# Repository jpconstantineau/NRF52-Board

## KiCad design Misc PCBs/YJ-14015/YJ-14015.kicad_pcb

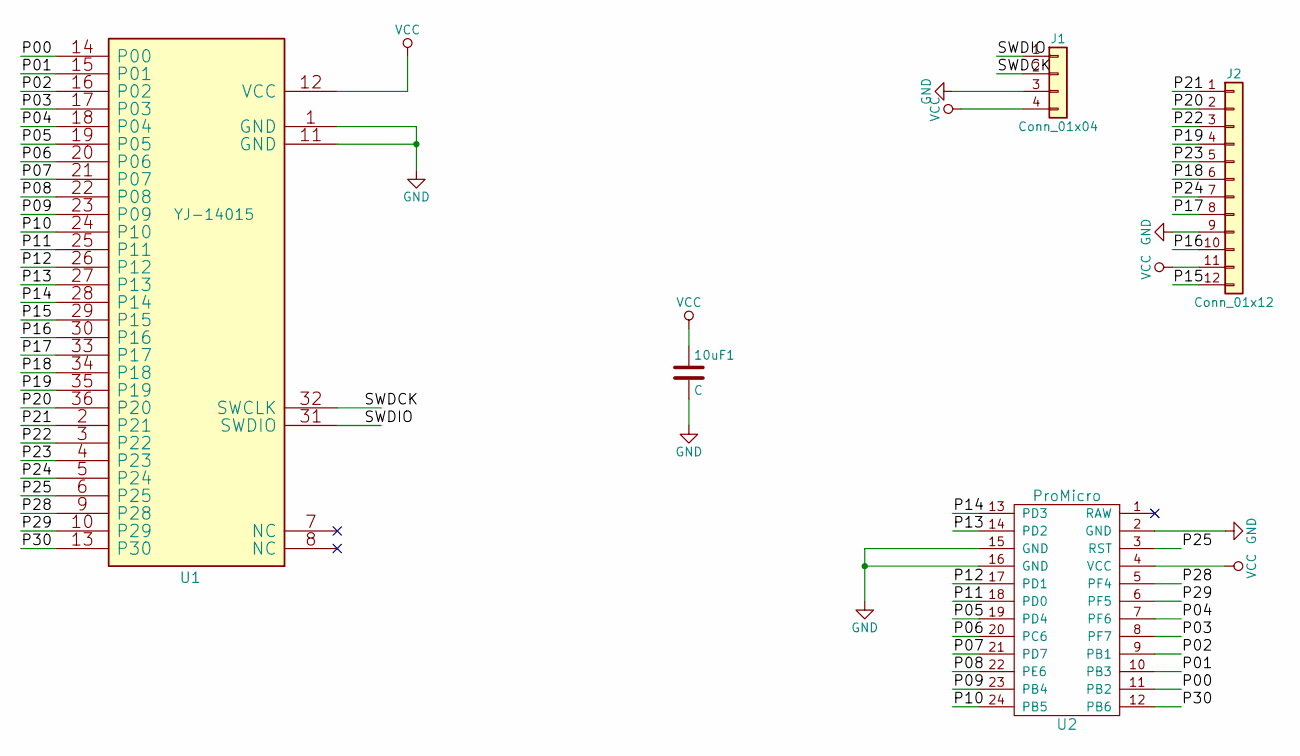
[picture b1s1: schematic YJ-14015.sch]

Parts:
10uF1: C; C_0805_HandSoldering
J1: Conn_01x04; Pin_Header_Straight_1x04_Pitch2.54mm
J2: Conn_01x12; Pin_Header_Straight_2x06_Pitch2.54mm
U1: YJ-14015
U2: ProMicro; Pro_Micro

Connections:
/P00: U1.14 (P00), U2.11 (PB2)
/P01: U1.15 (P01), U2.10 (PB3)
/P02: U1.16 (P02), U2.9 (PB1)
/P03: U1.17 (P03), U2.8 (PF7)
/P04: U1.18 (P04), U2.7 (PF6)
/P05: U1.19 (P05), U2.19 (PD4)
/P06: U1.20 (P06), U2.20 (PC6)
/P07: U1.21 (P07), U2.21 (PD7)
/P08: U1.22 (P08), U2.22 (PE6)
/P09: U1.23 (P09), U2.23 (PB4)
/P10: U1.24 (P10), U2.24 (PB5)
/P11: U1.25 (P11), U2.18 (PD0)
/P12: U1.26 (P12), U2.17 (PD1)
/P13: U1.27 (P13), U2.14 (PD2)
/P14: U1.28 (P14), U2.13 (PD3)
/P15: J2.12, U1.29 (P15)
/P16: J2.10, U1.30 (P16)
/P17: J2.8, U1.33 (P17)
/P18: J2.6, U1.34 (P18)
/P19: J2.4, U1.35 (P19)
/P20: J2.2, U1.36 (P20)
/P21: J2.1, U1.2 (P21)
/P22: J2.3, U1.3 (P22)
/P23: J2.5, U1.4 (P23)
/P24: J2.7, U1.5 (P24)
/P25: U1.6 (P25), U2.3 (RST)
/P28: U1.9 (P28), U2.5 (PF4)
/P29: U1.10 (P29), U2.6 (PF5)
/P30: U1.13 (P30), U2.12 (PB6)
/SWDCK: J1.2, U1.32 (SWCLK)
/SWDIO: J1.1, U1.31 (SWDIO)
GND: 10uF1.2, J1.3, J2.9, U1.1 (GND), U1.11 (GND), U2.2 (GND), U2.15 (GND), U2.16 (GND)
VCC: 10uF1.1, J1.4, J2.11, U1.12 (VCC), U2.4 (VCC)

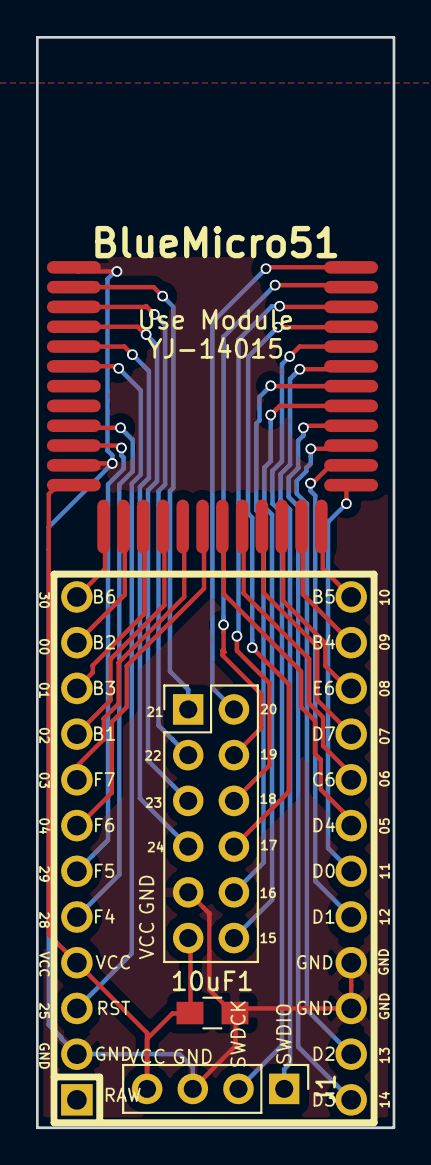
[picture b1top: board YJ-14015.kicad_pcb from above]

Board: 2 copper layers, 19.8 x 60.6 mm, 5 parts (1 on the bottom side), 33 nets.

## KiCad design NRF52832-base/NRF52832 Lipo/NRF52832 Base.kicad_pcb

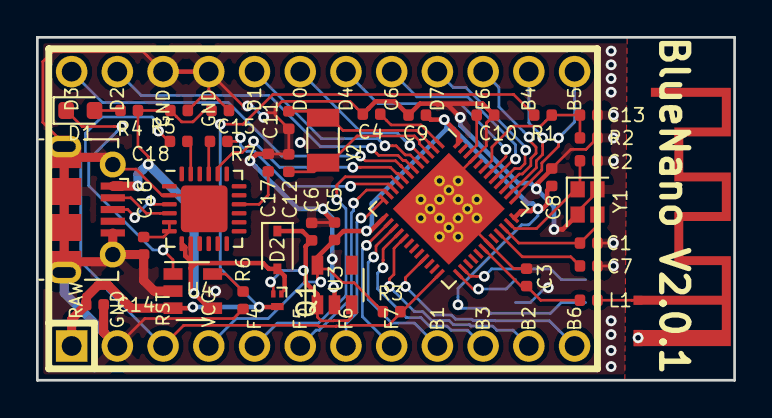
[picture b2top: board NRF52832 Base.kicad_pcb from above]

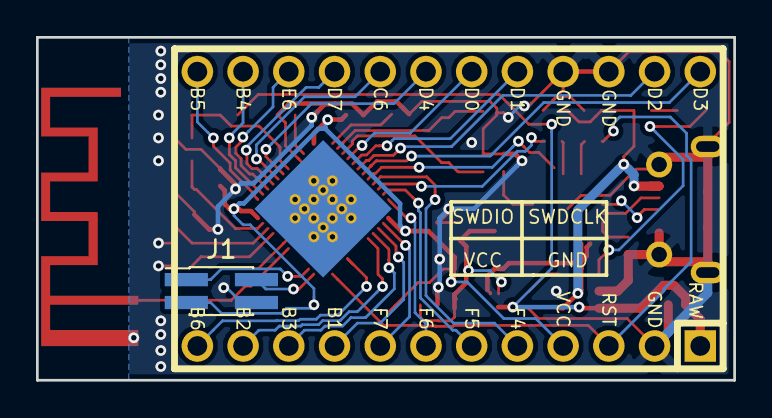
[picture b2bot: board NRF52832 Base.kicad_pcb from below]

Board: 2 copper layers, 38.7 x 19.0 mm, 39 parts (2 on the bottom side), 47 nets.

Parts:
AE1: Antenna_Shield; ti-an043-antenna-flipped
C1, C2, C11, C12: 12pF; C_0402_1005Metric
C3: 0.8pF; C_0402_1005Metric
C4, C5, C8: 100nF; C_0402_1005Metric
C6, C14, C15, C17: 10uF; C_0402_1005Metric
C7: 100pF; C_0402_1005Metric
C9: 4.7uF; C_0402_1005Metric
C10: 1uF; C_0402_1005Metric
C13: 1nF; C_0402_1005Metric
C16, C18: 0.1uF; C_0402_1005Metric
D1: LED; LED_0603_1608Metric
D2: B140WS-7; D_SOD-323
J1: Conn_01x06; PinHeader_2x02_P1.27mm_Vertical_SMD
J2: USB_B_Micro; USB_Micro-B_Molex-105017-0001
L1: 3.9nH; L_0402_1005Metric
Q1: CJ3139K; Diodes_DFN1006-3
R1: 806k; R_0402_1005Metric
R2: 2M; R_0402_1005Metric
R3, R6: 10k; R_0402_1005Metric
R4: 330; R_0402_1005Metric
R5: 100k; R_0402_1005Metric
R7: 1k; R_0402_1005Metric
U1: NRF52832-QFAA-R; QFN-48-1EP_6x6mm_P0.4mm_EP4.66x4.66mm_ThermalVias
U2: ProMicro; Pro_Micro
U3: AP2112K-3.3; SOT-23-5
U4: TP4054ST; SOT-23-5
U5: CP2104; QFN-24-1EP_4x4mm_P0.5mm_EP2.6x2.6mm
Y1: 32MHz; Crystal_SMD_2016-4Pin_2.0x1.6mm
Y2: 32.768kHz; Crystal_SMD_3215-2Pin_3.2x1.5mm

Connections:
/D+: J2.3, U5.3
/D-: J2.2, U5.4
/P0.02: U1.4, U2.18
/P0.03: U1.5, U2.17
/P0.04: U1.6, U2.14
/P0.05: U1.7, U2.13
/P0.07: U1.9, U2.5
/P0.09: U1.11, U2.6
/P0.10: U1.12, U2.7
/P0.11: U1.14, U2.8
/P0.18: U1.21, U2.12
/P0.27: U1.39, U2.22
/P0.28: U1.40, U2.21
/P0.29: U1.41, U2.20
/P0.30: U1.42, U2.19
/VBus: C15.1, D2.2, J2.1, Q1.1, R4.1, R5.1, U4.4, U5.7, U5.8
GND: AE1.2, C1.1, C2.1, C3.2, C4.2, C5.2, C6.2, C7.1, C8.2, C9.2, C10.2, C11.2, C12.2, C13.2, C14.2, C15.2, C16.2, C17.2, J1.4, J2.5, J2.6, R2.2, R5.2, R6.2, U1.31, U1.45, U1.49, U2.2, U2.15, U2.16, U3.2, U4.2, U5.2, U5.25, Y1.2, Y1.4
MISO: U1.17, U2.11
MOSI: U1.16, U2.10
unnamed: AE1.1, L1.2
unnamed: C1.2, U1.34, Y1.3
unnamed: C2.2, U1.35, Y1.1
unnamed: C3.1, L1.1, U1.30
unnamed: C4.1, U1.1
unnamed: C6.1, D2.1, Q1.2, U3.1, U3.3
unnamed: C7.2, U1.33
unnamed: C10.1, U1.46
unnamed: C11.1, U1.2, Y2.1
unnamed: C12.1, U1.3, Y2.2
unnamed: C16.1, U5.5, U5.6
unnamed: C17.1, U5.16
unnamed: C18.2, U5.23
unnamed: D1.1, U4.1
unnamed: D1.2, R4.2
unnamed: R6.1, U4.5
unnamed: R7.2, U5.21
RAW: C14.1, Q1.3, R1.1, U2.1, U4.3
RESET: C18.1, R3.2, U1.24, U2.3
RXD: R7.1, U1.10
SCK: U1.15, U2.9
SCL: U1.38, U2.23
SDA: U1.37, U2.24
SWDCLK: J1.2, U1.25
SWDIO: J1.1, U1.26
TXD: U1.8, U5.20
VBATT: C13.1, R1.2, R2.1, U1.43
VCC: C5.1, C8.1, C9.1, J1.3, R3.1, U1.13, U1.36, U1.48, U2.4, U3.5

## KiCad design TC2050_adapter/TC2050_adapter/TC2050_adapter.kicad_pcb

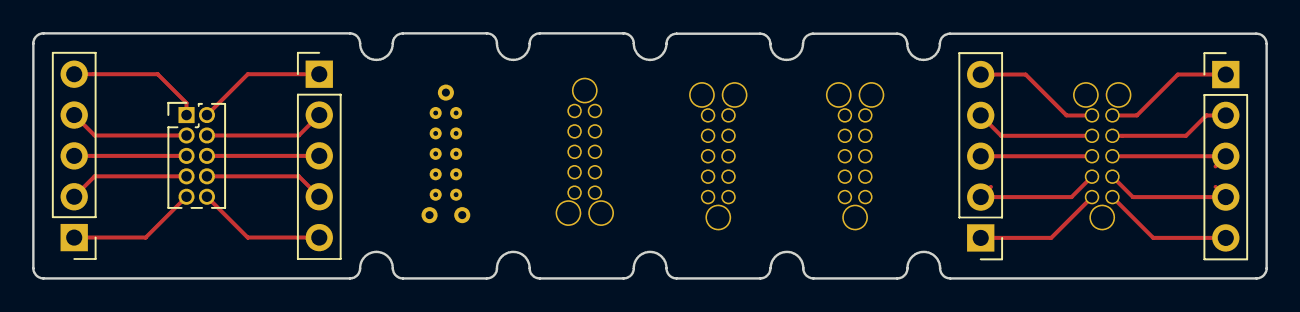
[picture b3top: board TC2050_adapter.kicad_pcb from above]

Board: 2 copper layers, 76.7 x 15.2 mm, 10 parts (0 on the bottom side), 20 nets.

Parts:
J1, J3, J4, J6: Conn_01x05; PinHeader_1x05_P2.54mm_Vertical
J2: Cortex Debug 10-pin connector; PinHeader_2x05_P1.27mm_Vertical
J5, J8, J9, J11: TC2050_pogo
J7: TC2050_pogo_alignment; TC2050_alignment

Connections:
unnamed: J1.1, J2.9
unnamed: J1.2, J2.7
unnamed: J1.3, J2.5
unnamed: J1.4, J2.3
unnamed: J1.5, J2.1
unnamed: J2.2, J3.1
unnamed: J2.4, J3.2
unnamed: J2.6, J3.3
unnamed: J2.8, J3.4
unnamed: J2.10, J3.5
unnamed: J4.1, J5.5
unnamed: J4.2, J5.4
unnamed: J4.3, J5.3
unnamed: J4.4, J5.2
unnamed: J4.5, J5.1
unnamed: J5.6, J6.5
unnamed: J5.7, J6.4
unnamed: J5.8, J6.3
unnamed: J5.9, J6.2
unnamed: J5.10, J6.1

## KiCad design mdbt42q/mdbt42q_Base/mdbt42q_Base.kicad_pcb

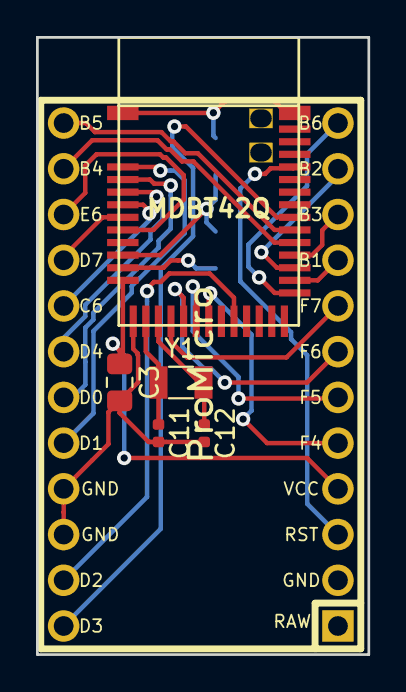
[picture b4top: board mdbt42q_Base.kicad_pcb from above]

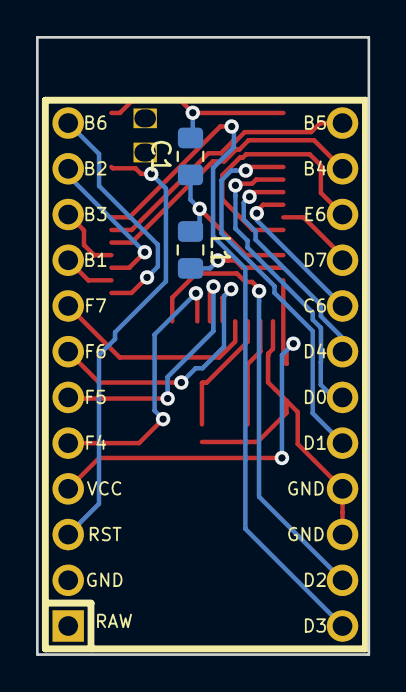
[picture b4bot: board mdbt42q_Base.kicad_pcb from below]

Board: 2 copper layers, 18.4 x 34.3 mm, 8 parts (2 on the bottom side), 25 nets.

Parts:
C1: 1uF; C_0805_2012Metric_Pad1.15x1.40mm_HandSolder
C3: 10uF; C_0805_2012Metric_Pad1.15x1.40mm_HandSolder
C11, C12: 12pF; C_0402_1005Metric
L1: 10uH; L_0805_2012Metric_Pad1.15x1.40mm_HandSolder
U1: MDBT42Q
U2: ProMicro; Pro_Micro
Y1: 32.768kHz; Crystal_SMD_3215-2Pin_3.2x1.5mm

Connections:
/MISO: U1.28, U2.10
/MOSI: U1.27, U2.11
/P0.02: U1.15, U2.8
/P0.03: U1.16, U2.7
/P0.04: U1.17, U2.6
/P0.05: U1.18, U2.5
/P0.07: U1.20, U2.14
/P0.11: U1.25, U2.12
/P0.15: U1.29, U2.23
/P0.16: U1.30, U2.24
/P0.17: U1.31, U2.13
/P0.27: U1.4, U2.19
/P0.28: U1.5, U2.20
/P0.29: U1.6, U2.21
/P0.30: U1.7, U2.22
/RESET: U1.35, U2.3
/SCK: U1.26, U2.9
/SCL: U1.3, U2.18
/SDA: U1.2, U2.17
GND: C1.2, C3.2, C11.2, C12.2, U1.1, U1.12, U1.24, U1.39, U2.2, U2.15, U2.16
unnamed: C1.1, L1.1, U1.9
unnamed: C11.1, U1.13, Y1.1
unnamed: C12.1, U1.14, Y1.2
unnamed: L1.2, U1.10
VCC: C3.1, U1.11, U2.4
